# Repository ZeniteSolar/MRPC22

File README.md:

# MRPC22
Variação do Módulo Raspberry Pi CAN 2019 (MRPC19) projetada para a Raspberry Pi 3 Model B+

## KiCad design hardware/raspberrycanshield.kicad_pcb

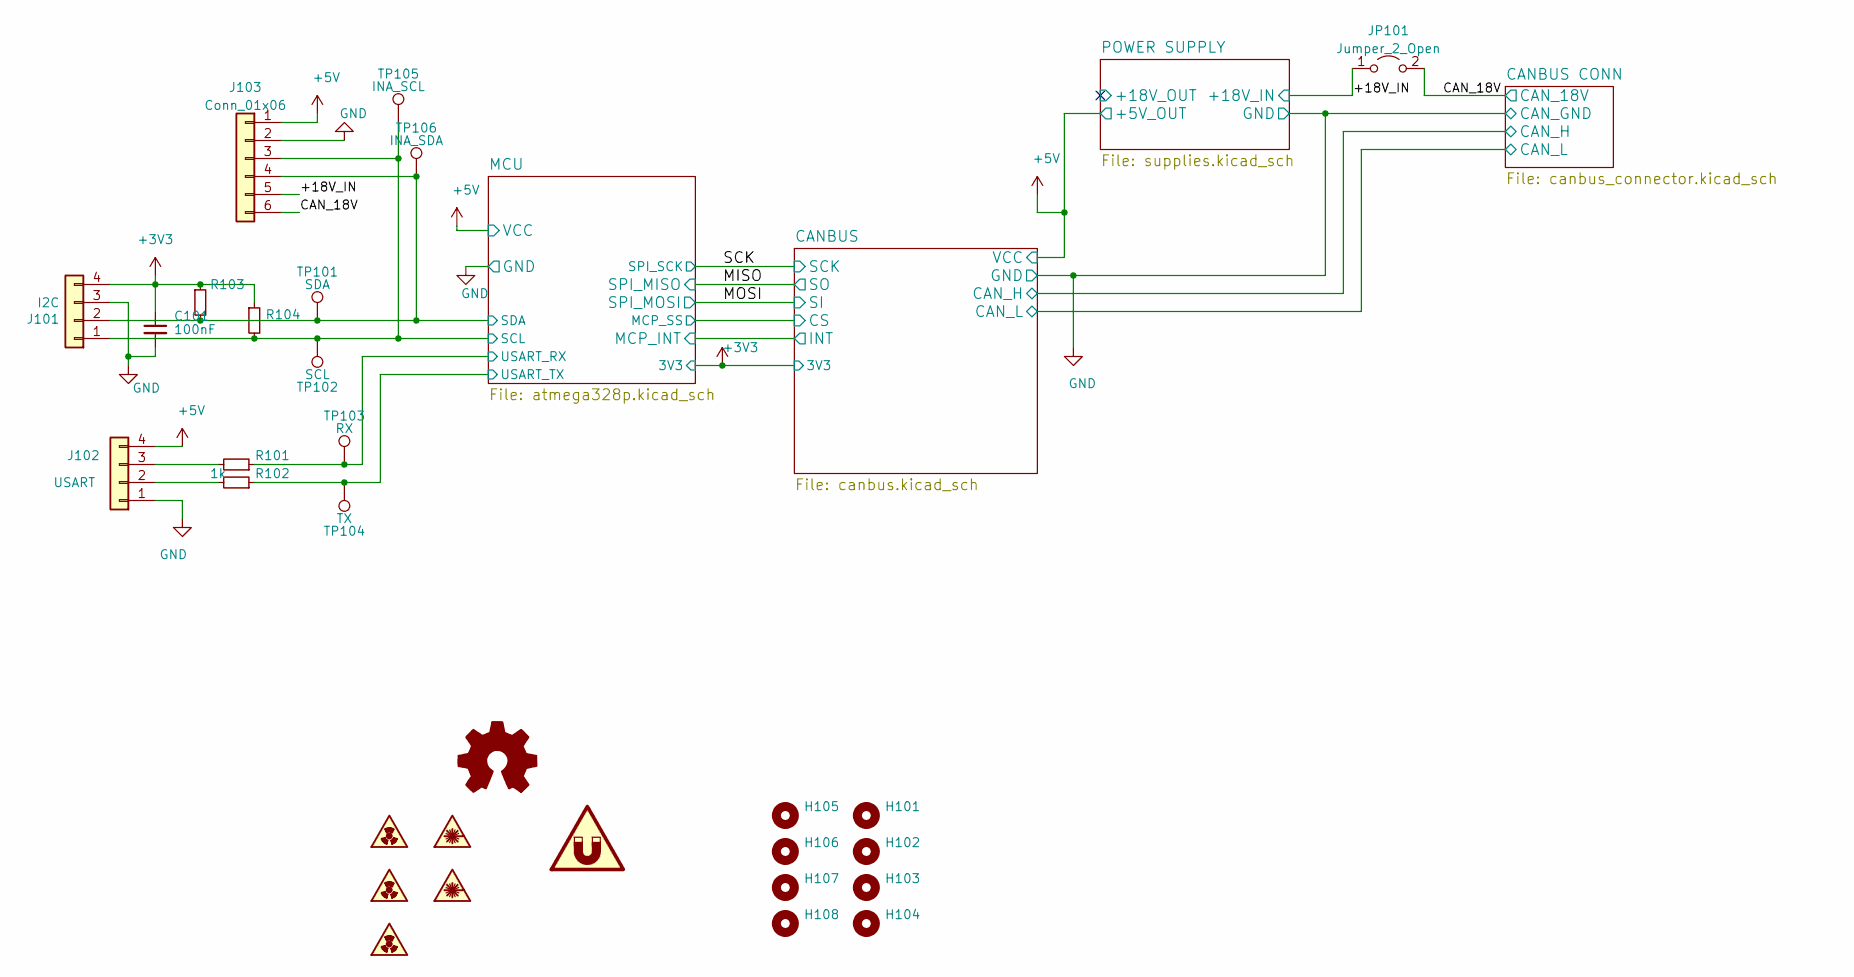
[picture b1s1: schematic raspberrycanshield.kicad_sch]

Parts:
C101: 100nF; C_0603_1608Metric_Pad1.08x0.95mm_HandSolder
H101, H102, H103, H104: MountingHole_3.2mm_M3
H105, H106, H107, H108: MountingHole_2.7mm_M2.5
J101: I2C; PinHeader_1x04_P2.54mm_Horizontal
J102: USART; PinHeader_1x04_P2.54mm_Horizontal
J103: Conn_01x06; PinHeader_1x06_P2.54mm_Vertical
JP101: Jumper_2_Open; SolderJumper-2_P1.3mm_Open_RoundedPad1.0x1.5mm
LOGO101: Logo_Open_Hardware_Small; OSHW-Logo2_7.3x6mm_SilkScreen
R101, R103, R104: (no value)
R102: 1k; R_0603_1608Metric_Pad0.98x0.95mm_HandSolder
SYM101, SYM103: SYM_Radioactive_Radiation_Small; symbol_logoZenite
SYM102: SYM_Magnet_Large; raspberrypi_2_3
SYM104: SYM_Radioactive_Radiation_Small; symbol_naolavar
SYM105, SYM106: SYM_LASER_Small; synbol_logoifsc
TP101: SDA; TestPoint_Pad_2.0x2.0mm
TP102: SCL; TestPoint_Pad_2.0x2.0mm
TP103: RX; TestPoint_Pad_2.0x2.0mm
TP104: TX; TestPoint_Pad_2.0x2.0mm
TP105: INA_SCL; TestPoint_Pad_2.0x2.0mm
TP106: INA_SDA; TestPoint_Pad_2.0x2.0mm

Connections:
+3V3: C101.1, J101.4, R103.1, R104.1; also elsewhere on the board
+5V: J102.4, J103.1; also elsewhere on the board
/+18V_IN: J103.5, JP101.1 (A); also elsewhere on the board
/CAN_18V: J103.6, JP101.2 (B); also elsewhere on the board
/MCU/SCL: J101.1, J103.3, R104.2, TP102.1, TP105.1; also elsewhere on the board
/MCU/SDA: J101.2, J103.4, R103.2, TP101.1, TP106.1; also elsewhere on the board
/MCU/USART_RX: R101.1, TP103.1; also elsewhere on the board
/MCU/USART_TX: R102.1, TP104.1; also elsewhere on the board
GND: C101.2, J101.3, J102.1, J103.2; also elsewhere on the board
unnamed: J102.2, R102.2
unnamed: J102.3, R101.2

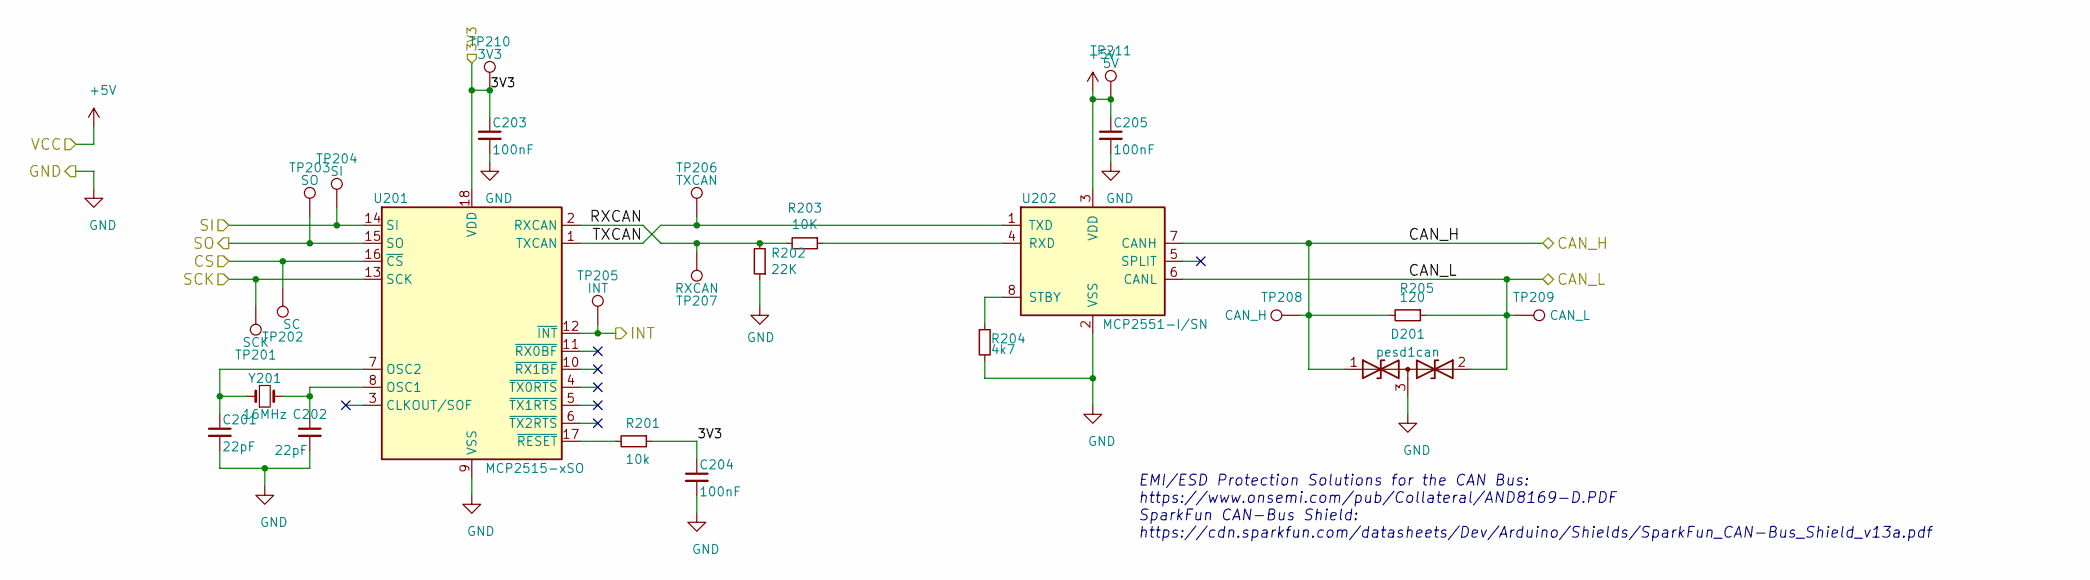
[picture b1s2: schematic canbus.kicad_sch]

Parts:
C201, C202: 22pF; C_0603_1608Metric_Pad1.08x0.95mm_HandSolder
C203, C204, C205: 100nF; C_0603_1608Metric_Pad1.08x0.95mm_HandSolder
D201: pesd1can; SOT-23
R201: 10k; R_0603_1608Metric_Pad0.98x0.95mm_HandSolder
R202: 22K; R_0603_1608Metric_Pad0.98x0.95mm_HandSolder
R203: 10K; R_0603_1608Metric_Pad0.98x0.95mm_HandSolder
R204: 4k7; R_0805_2012Metric_Pad1.20x1.40mm_HandSolder
R205: 120; R_0805_2012Metric_Pad1.20x1.40mm_HandSolder
TP201: SCK; TestPoint_Pad_2.0x2.0mm
TP202: SC; TestPoint_Pad_2.0x2.0mm
TP203: SO; TestPoint_Pad_2.0x2.0mm
TP204: SI; TestPoint_Pad_2.0x2.0mm
TP205: INT; TestPoint_Pad_2.0x2.0mm
TP206: TXCAN; TestPoint_Pad_2.0x2.0mm
TP207: RXCAN; TestPoint_Pad_2.0x2.0mm
TP208: CAN_H; TestPoint_Pad_2.0x2.0mm
TP209: CAN_L; TestPoint_Pad_2.0x2.0mm
TP210: 3V3; TestPoint_Pad_2.0x2.0mm
TP211: 5V; TestPoint_Pad_2.0x2.0mm
U201: MCP2515-xSO; SOIC-18W_7.5x11.6mm_P1.27mm
U202: MCP2551-I/SN; SOIC-8_3.9x4.9mm_P1.27mm
Y201: 16MHz; Crystal_HC49-U_Vertical

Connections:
+3V3: C203.1, C204.1, R201.1, TP210.1, U201.18 (VDD); also elsewhere on the board
+5V: C205.1, TP211.1, U202.3 (VDD); also elsewhere on the board
/CANBUS CONN/CAN_H: D201.1 (A1), R205.2, TP208.1, U202.7 (CANH); also elsewhere on the board
/CANBUS CONN/CAN_L: D201.2 (A2), R205.1, TP209.1, U202.6 (CANL); also elsewhere on the board
/CANBUS/CS: TP202.1, U201.16 (~CS); also elsewhere on the board
/CANBUS/INT: TP205.1, U201.12 (~INT); also elsewhere on the board
/CANBUS/RXCAN: R202.2, R203.2, TP207.1, U201.2 (RXCAN)
/CANBUS/TXCAN: TP206.1, U201.1 (TXCAN), U202.1 (TXD)
/MISO: TP203.1, U201.15 (SO); also elsewhere on the board
/MOSI: TP204.1, U201.14 (SI); also elsewhere on the board
/SCK: TP201.1, U201.13 (SCK); also elsewhere on the board
GND: C201.2, C202.2, C203.2, C204.2, C205.2, D201.3 (common), R202.1, R204.2, U201.9 (VSS), U202.2 (VSS); also elsewhere on the board
unnamed: C201.1, U201.7 (OSC2), Y201.1
unnamed: C202.1, U201.8 (OSC1), Y201.2
unnamed: R201.2, U201.17 (~RESET)
unnamed: R203.1, U202.4 (RXD)
unnamed: R204.1, U202.8 (STBY)

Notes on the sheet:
EMI/ESD Protection Solutions for the CAN Bus: https://www.onsemi.com/pub/Collateral/AND8169-D.PDF SparkFun CAN-Bus Shield: https://cdn.sparkfun.com/datasheets/Dev/Arduino/Shields/SparkFun_CAN-Bus_Shield_v13a.pdf

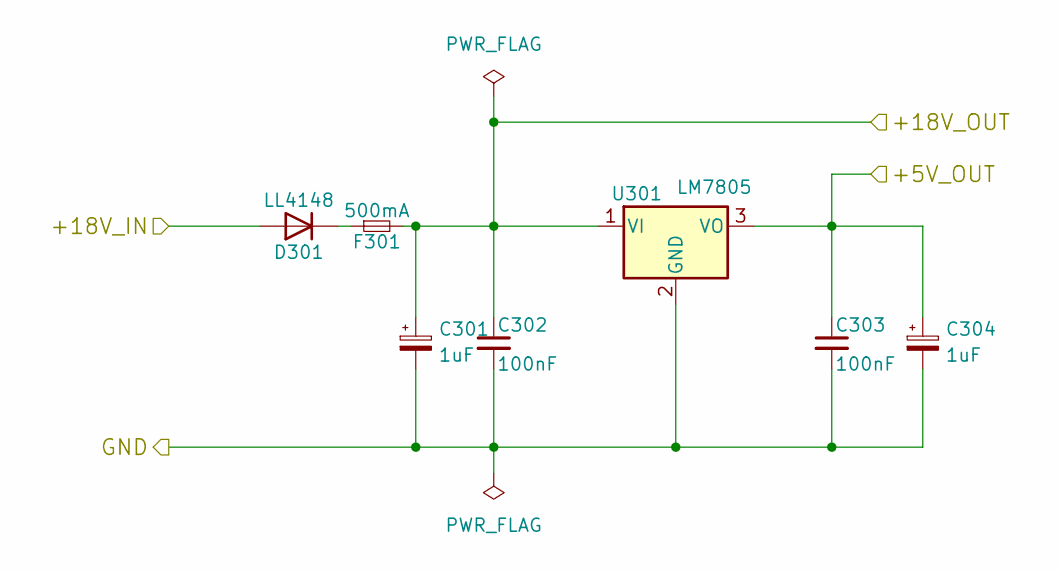
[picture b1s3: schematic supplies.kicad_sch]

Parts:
C301, C304: 1uF; C_1206_3216Metric_Pad1.33x1.80mm_HandSolder
C302, C303: 100nF; C_0603_1608Metric_Pad1.08x0.95mm_HandSolder
D301: LL4148; D_MiniMELF_Handsoldering
F301: 500mA; Fuse_1206_3216Metric_Pad1.42x1.75mm_HandSolder
U301: LM7805; TO-220-3_Horizontal_TabDown_SMD

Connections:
+5V: C303.1, C304.1, U301.3 (VO); also elsewhere on the board
/+18V_IN: D301.2 (A); also elsewhere on the board
/POWER SUPPLY/+18V_OUT: C301.1, C302.1, F301.2, U301.1 (VI)
GND: C301.2, C302.2, C303.2, C304.2, U301.2 (GND); also elsewhere on the board
unnamed: D301.1 (K), F301.1

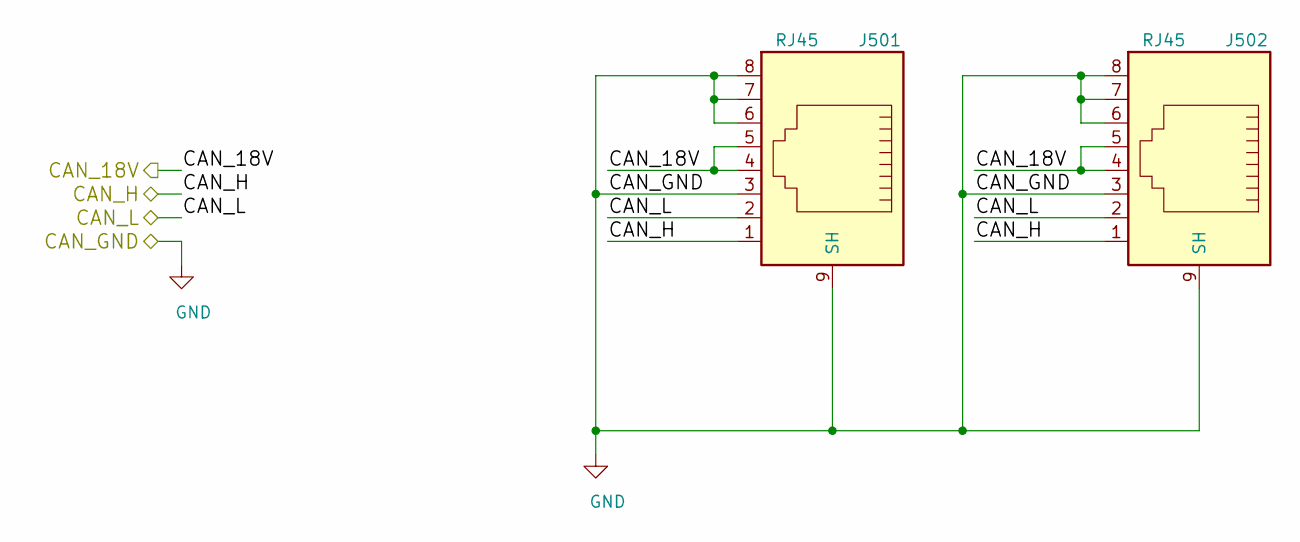
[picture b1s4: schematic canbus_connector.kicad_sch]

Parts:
J501, J502: RJ45; RJ45_YH59_01

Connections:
/CANBUS CONN/CAN_H: J501.1, J502.1; also elsewhere on the board
/CANBUS CONN/CAN_L: J501.2, J502.2; also elsewhere on the board
/CAN_18V: J501.4, J501.5, J502.4, J502.5; also elsewhere on the board
GND: J501.3, J501.6, J501.7, J501.8, J501.9 (SH), J502.3, J502.6, J502.7, J502.8, J502.9 (SH); also elsewhere on the board

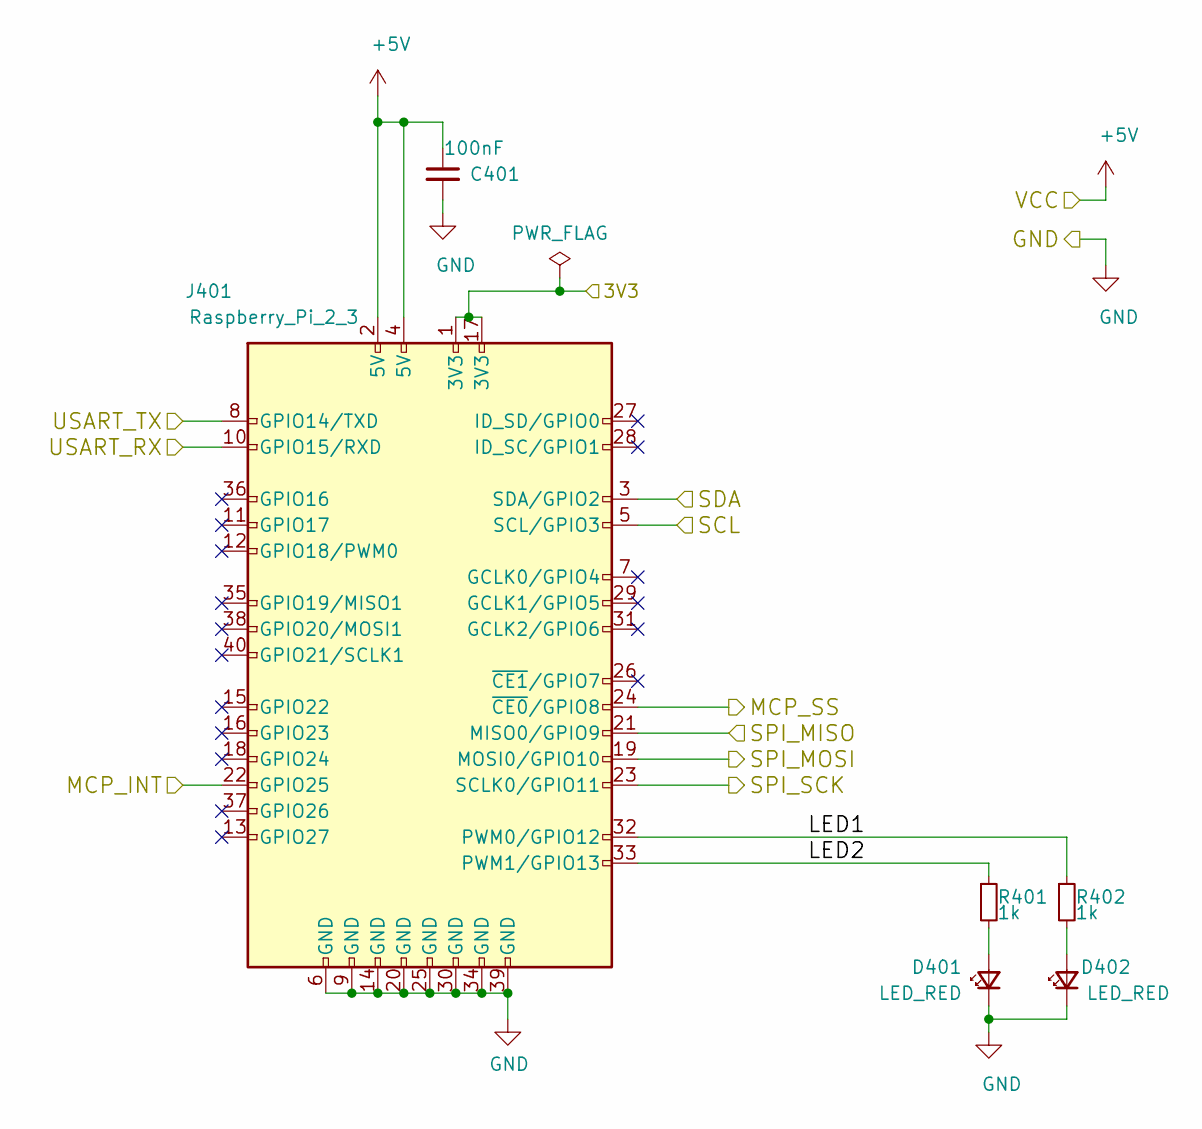
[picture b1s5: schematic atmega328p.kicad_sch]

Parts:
C401: 100nF; C_0603_1608Metric_Pad1.08x0.95mm_HandSolder
D401, D402: LED_RED; LED_0603_1608Metric_Pad1.05x0.95mm_HandSolder
J401: Raspberry_Pi_2_3; PinHeader_2x20_P2.54mm_Vertical
R401, R402: 1k; R_0603_1608Metric_Pad0.98x0.95mm_HandSolder

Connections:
+3V3: J401.1 (3V3), J401.17 (3V3); also elsewhere on the board
+5V: C401.1, J401.2 (5V), J401.4 (5V); also elsewhere on the board
/CANBUS/CS: J401.24 (~CE0/GPIO8); also elsewhere on the board
/CANBUS/INT: J401.22 (GPIO25); also elsewhere on the board
/MCU/LED1: J401.32 (PWM0/GPIO12), R402.1
/MCU/LED2: J401.33 (PWM1/GPIO13), R401.1
/MCU/SCL: J401.5 (SCL/GPIO3); also elsewhere on the board
/MCU/SDA: J401.3 (SDA/GPIO2); also elsewhere on the board
/MCU/USART_RX: J401.10 (GPIO15/RXD); also elsewhere on the board
/MCU/USART_TX: J401.8 (GPIO14/TXD); also elsewhere on the board
/MISO: J401.21 (MISO0/GPIO9); also elsewhere on the board
/MOSI: J401.19 (MOSI0/GPIO10); also elsewhere on the board
/SCK: J401.23 (SCLK0/GPIO11); also elsewhere on the board
GND: C401.2, D401.1 (K), D402.1 (K), J401.6 (GND), J401.9 (GND), J401.14 (GND), J401.20 (GND), J401.25 (GND), J401.30 (GND), J401.34 (GND), J401.39 (GND); also elsewhere on the board
unnamed: D401.2 (A), R401.2
unnamed: D402.2 (A), R402.2

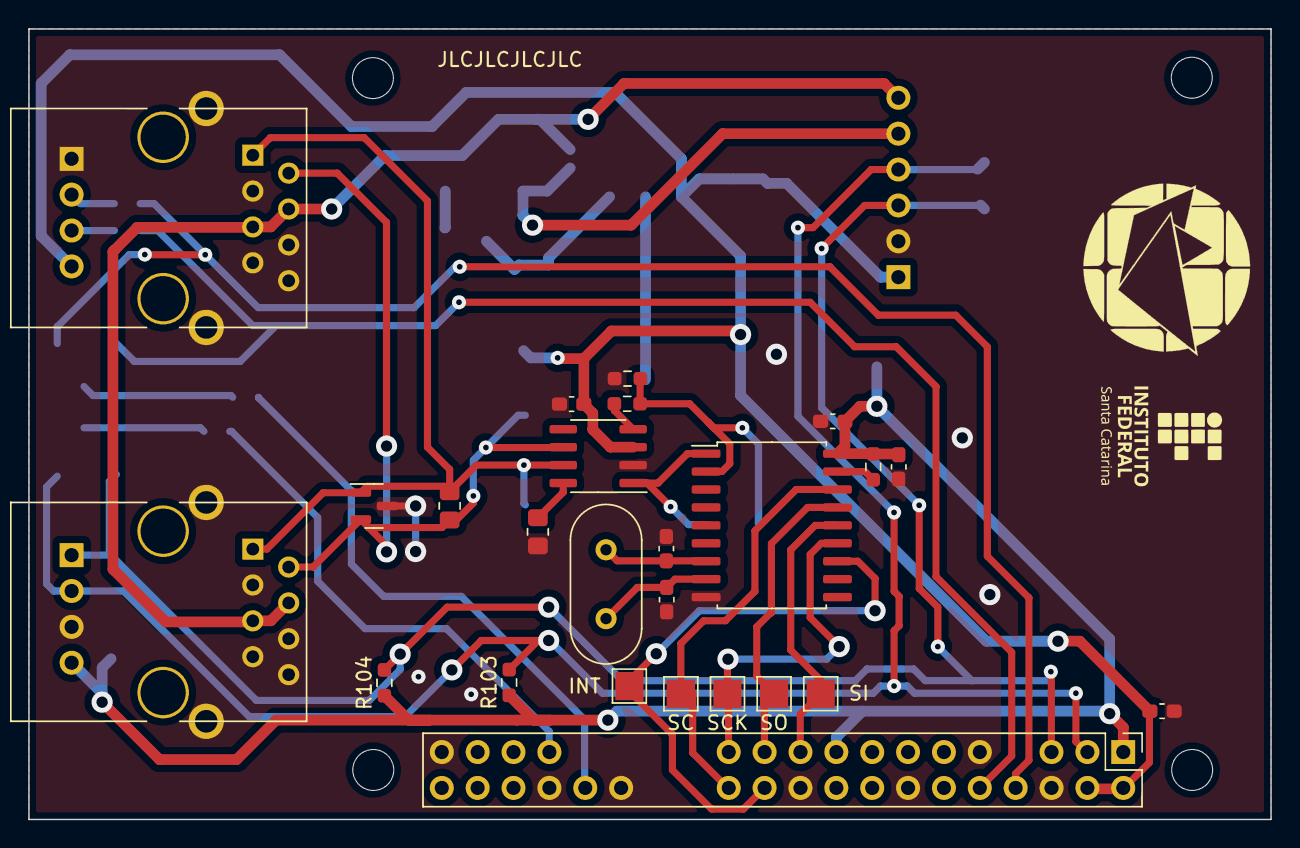
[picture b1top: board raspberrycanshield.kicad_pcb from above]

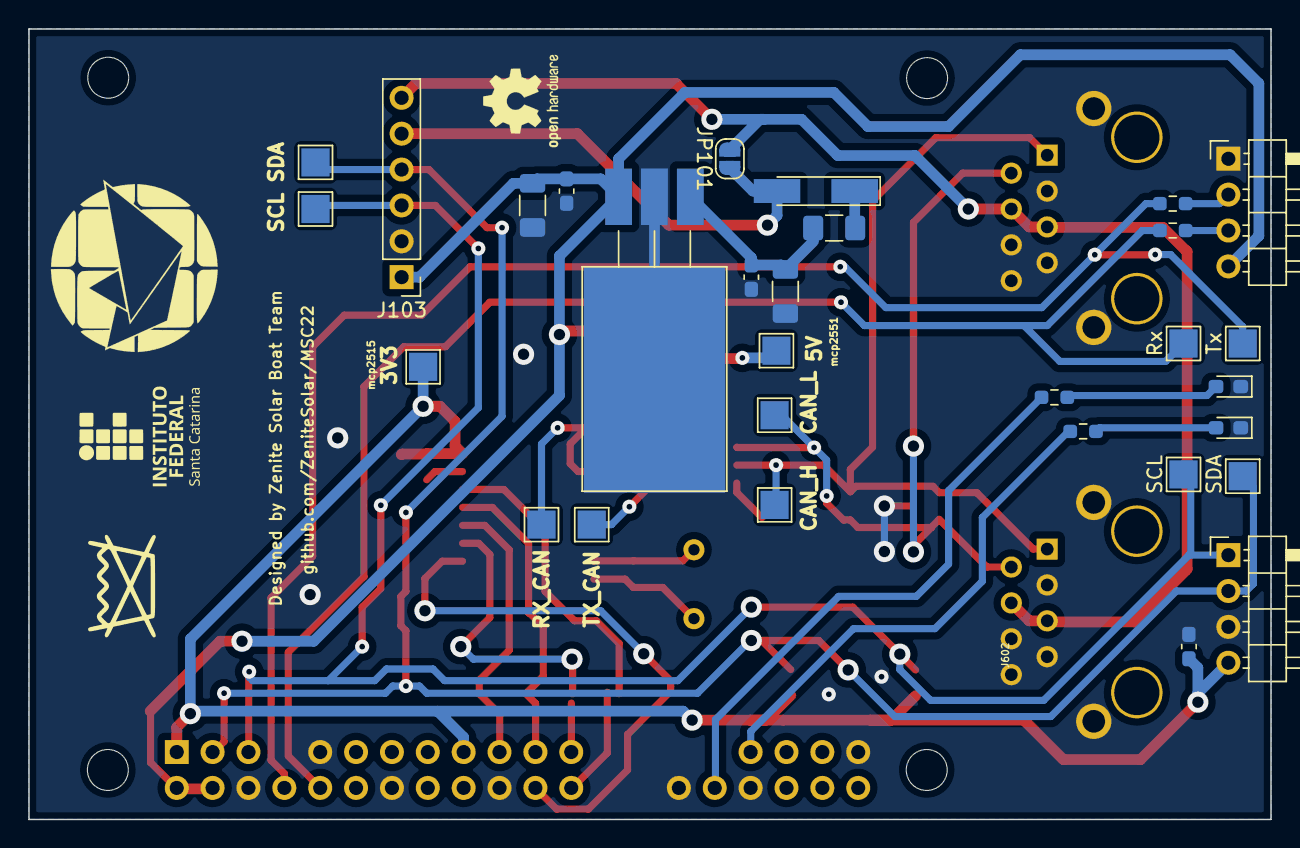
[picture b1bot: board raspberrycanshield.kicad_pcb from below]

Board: 2 copper layers, 88.0 x 56.0 mm, 65 parts (34 on the bottom side), 31 nets.

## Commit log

2022-06-29 hardware: kicad project
2022-06-29 Silkscreen update
2022-06-29 hardware: Silkscreen update
2022-06-30 Silkscreen updated with JLC. Finished.
2023-04-20 add BOM
